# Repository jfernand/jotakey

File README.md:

# Jotakey

A FIDO2 / WebAuthn security key, in the family of the YubiKey, written in Rust and
engineered as security-critical software: tested, fuzzed, mutation-tested, and with its
security-critical state machines proved in Lean 4.

It runs on two platforms:

- **The jotakey key** (`hardware/`): a USB-A dongle with an STM32L432 microcontroller and an
  Infineon OPTIGA Trust M secure element. Hardware 0.3.0 is designed and ready to order; its
  firmware (native USB, touch, and the OPTIGA over its shielded connection) is written and
  tested against a simulated OPTIGA, and awaits a board.
- **The Espressif ESP32-C6 DevKit**: the development platform, where the MVP firmware runs
  today (CTAP 2.0, non-resident credentials, USB through a Linux bridge, and BLE).

## Where to start

| | |
|---|---|
| `docs/jotakey.pdf` | The design report: FIDO and passkeys from first principles, the threat model, the key hierarchy, testing and formal verification. `docs/jotakey-print.pdf` is the same for paper. |
| `AGENTS.md` | The normative rules: security invariants, key hierarchy, coding rules, commands. |
| `hardware/HARDWARE.md` | The board: part choices against their datasheets. |
| `hardware/MANUFACTURING.md` | How to order a hardware release from JLCPCB. |
| `crates/jotakey-core` | The protocol core: `no_std`, no allocation, no `unsafe`. |
| `formal/` | Lean 4 models and proofs. |
| `crates/jotakey-explorer` | `just explore`: a terminal browser for the FIDO keys attached to this computer, any make. |
| `examples/webauthn-topcoat` | A demo web app: register a Jotakey and sign in with it, on `localhost`. |

## Versions

Hardware and firmware are versioned separately: hardware releases are tagged `hw-vX.Y.Z`,
firmware releases `fw-vX.Y.Z`. Each release publishes both versions of the report.

## License

Copyright (c) 2026 Javier Fernandez @ JotaSoft.

Licensed under either of [Apache License, Version 2.0](LICENSE-APACHE) or
[MIT license](LICENSE-MIT), at your option.

Unless you explicitly state otherwise, any contribution intentionally submitted for inclusion
in this work, as defined in the Apache-2.0 license, shall be dual licensed as above, without any
additional terms or conditions.

Third-party documents cited by the design are not part of this repository; see
`docs/references/README.md` and `hardware/datasheets/README.md` for where to obtain them.

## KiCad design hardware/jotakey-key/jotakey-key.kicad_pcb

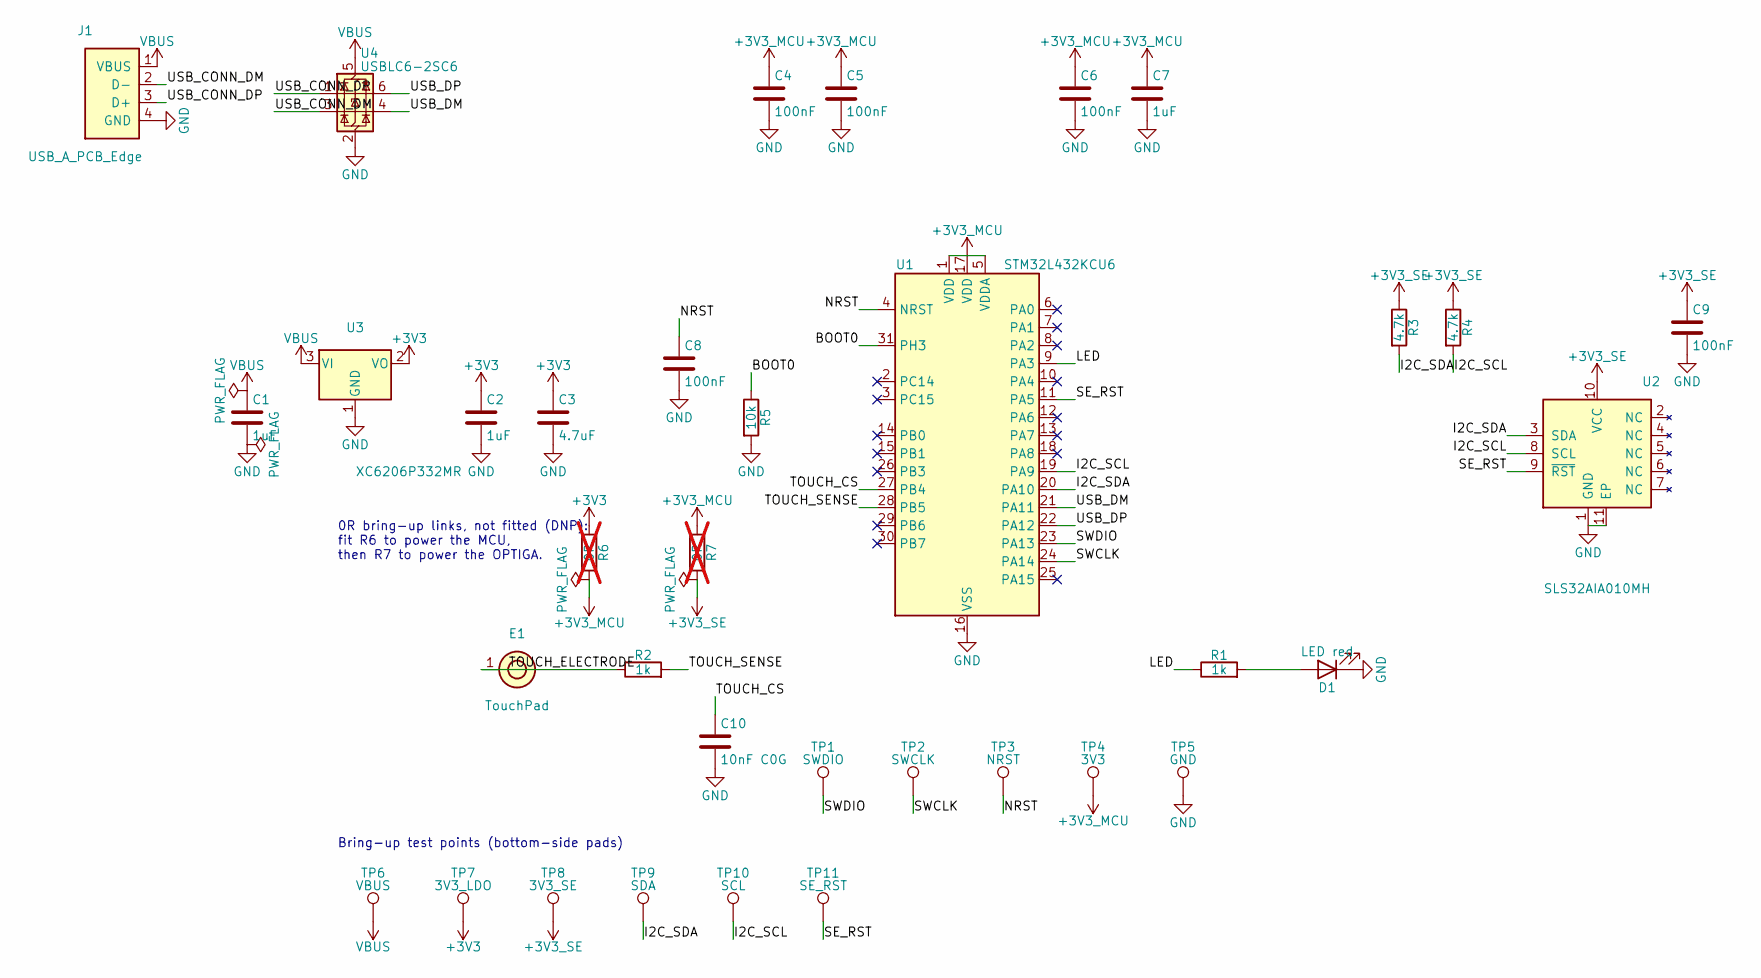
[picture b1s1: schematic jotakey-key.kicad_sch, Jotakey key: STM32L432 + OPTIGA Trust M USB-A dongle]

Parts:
C1, C2, C7: 1uF; C_0402_1005Metric; MPN CL05A105KA5NQNC; LCSC C52923
C3: 4.7uF; C_0603_1608Metric; MPN CL10A475KO8NNNC; LCSC C19666
C4, C5, C6, C8, C9: 100nF; C_0402_1005Metric; MPN CL05B104KO5NNNC; LCSC C1525
C10: 10nF C0G; C_0402_1005Metric; MPN GRM1555C1H103JE01D; LCSC C22400107
D1: LED red; LED_0603_1608Metric; MPN KT-0603R; LCSC C2286
E1: TouchPad; TouchPad_D10mm
J1: USB_A_PCB_Edge; USB_A_PCB_Edge_2.0mm
R1, R2: 1k; R_0402_1005Metric; MPN 0402WGF1001TCE; LCSC C11702
R3, R4: 4.7k; R_0402_1005Metric; MPN 0402WGF4701TCE; LCSC C25900
R5: 10k; R_0402_1005Metric; MPN 0402WGF1002TCE; LCSC C25744
R6, R7: 0R; R_0402_1005Metric; MPN 0402WGF0000TCE; LCSC C17168; not fitted
TP1: SWDIO; TestPoint_Pad_D1.0mm
TP2: SWCLK; TestPoint_Pad_D1.0mm
TP3: NRST; TestPoint_Pad_D1.0mm
TP4: 3V3; TestPoint_Pad_D1.0mm
TP5: GND; TestPoint_Pad_D1.0mm
TP6: VBUS; TestPoint_Pad_D1.0mm
TP7: 3V3_LDO; TestPoint_Pad_D1.0mm
TP8: 3V3_SE; TestPoint_Pad_D1.0mm
TP9: SDA; TestPoint_Pad_D1.0mm
TP10: SCL; TestPoint_Pad_D1.0mm
TP11: SE_RST; TestPoint_Pad_D1.0mm
U1: STM32L432KCU6; QFN-32-1EP_5x5mm_P0.5mm_EP3.45x3.45mm; MPN STM32L432KCU6; LCSC C1337280
U2: SLS32AIA010MH; Infineon_PG-USON-10-2_3x3mm_P0.5mm_EP1.7x2.5mm; MPN SLS32AIA010MH USON10; LCSC C539250
U3: XC6206P332MR; SOT-23-3; MPN XC6206P332MR-G; LCSC C5446
U4: USBLC6-2SC6; SOT-23-6; MPN USBLC6-2SC6; LCSC C7519

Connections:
+3V3: C2.1, C3.1, R6.1, TP7.1 (1_1), U3.2 (VO)
+3V3_MCU: C4.1, C5.1, C6.1, C7.1, R6.2, R7.1, TP4.1 (1_1), U1.1 (VDD), U1.5 (VDDA), U1.17 (VDD)
+3V3_SE: C9.1, R3.1, R4.1, R7.2, TP8.1 (1_1), U2.10 (VCC)
/BOOT0: R5.1, U1.31 (PH3)
/I2C_SCL: R4.2, TP10.1 (1_1), U1.19 (PA9), U2.8 (SCL)
/I2C_SDA: R3.2, TP9.1 (1_1), U1.20 (PA10), U2.3 (SDA)
/LED: R1.1, U1.9 (PA3)
/NRST: C8.1, TP3.1 (1_1), U1.4 (NRST)
/SE_RST: TP11.1 (1_1), U1.11 (PA5), U2.9 (~RST)
/SWCLK: TP2.1 (1_1), U1.24 (PA14)
/SWDIO: TP1.1 (1_1), U1.23 (PA13)
/TOUCH_CS: C10.1, U1.27 (PB4)
/TOUCH_ELECTRODE: E1.1 (~_1), R2.1
/TOUCH_SENSE: R2.2, U1.28 (PB5)
/USB_CONN_DM: J1.2 (D-), U4.3 (I/O2)
/USB_CONN_DP: J1.3 (D+), U4.1 (I/O1)
/USB_DM: U1.21 (PA11), U4.4 (I/O2)
/USB_DP: U1.22 (PA12), U4.6 (I/O1)
GND: C1.2, C2.2, C3.2, C4.2, C5.2, C6.2, C7.2, C8.2, C9.2, C10.2, D1.1 (K), J1.4 (GND), R5.2, TP5.1 (1_1), U1.16 (VSS), U1.32 (VSS), U1.33 (VSS), U2.1 (GND), U2.11 (EP), U3.1 (GND), U4.2 (GND)
unnamed: D1.2 (A), R1.2
VBUS: C1.1, J1.1 (VBUS), TP6.1 (1_1), U3.3 (VI), U4.5 (VBUS)

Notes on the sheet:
0R bring-up links, not fitted (DNP): fit R6 to power the MCU, then R7 to power the OPTIGA.
Bring-up test points (bottom-side pads)

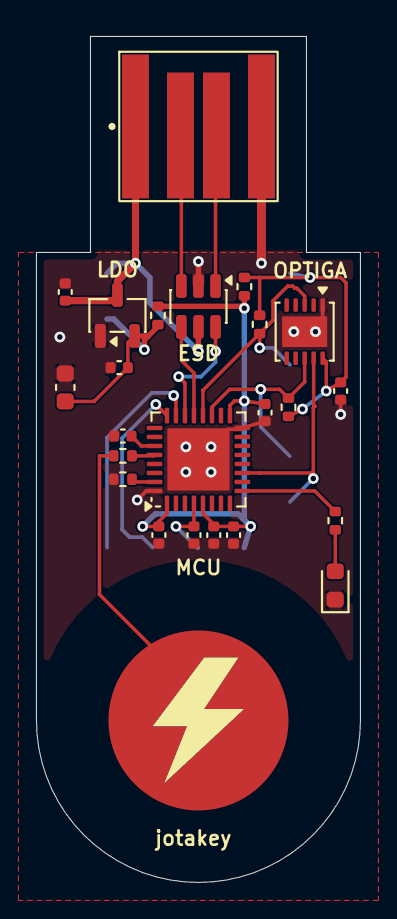
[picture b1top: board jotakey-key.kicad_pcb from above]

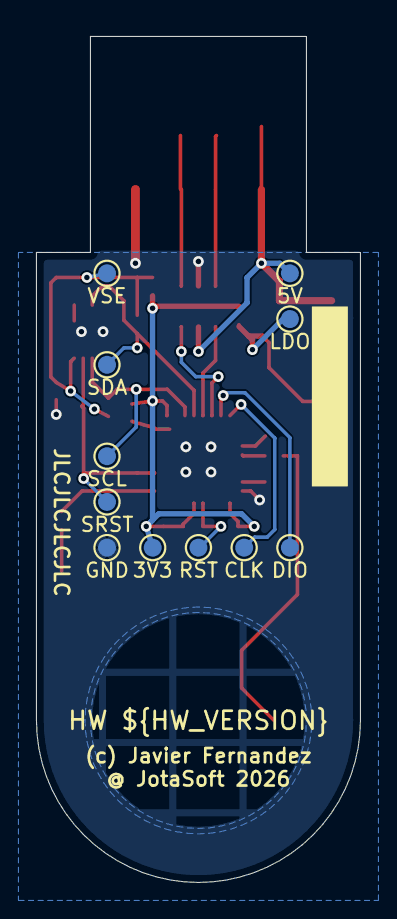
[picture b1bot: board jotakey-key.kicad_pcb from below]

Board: 2 copper layers, 18.0 x 47.0 mm, 35 parts (11 on the bottom side), 21 nets.

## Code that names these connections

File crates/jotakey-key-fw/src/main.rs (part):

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    defmt::info!("jotakey key {} booting", env!("CARGO_PKG_VERSION"));

    // LED first, so faults are visible.
    let led = Output::new(p.PA3, Level::Low, Speed::Low);
    if let Ok(t) = led::led_task(led) {
        spawner.spawn(t);
    }
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    let out = OUT.init([0u8; MAX_MSG_SIZE]);

    // USB starts early so that a faulty key still enumerates and answers CTAP1_ERR_OTHER.
    let driver = stm_usb::Driver::new(p.USB, Irqs, p.PA12, p.PA11);
    interrupt::SPI3.set_priority(Priority::P6);
    let usb_spawner = USB_EXECUTOR.start(interrupt::SPI3);
    if let Ok(t) = usb::usb_task(driver) {
        usb_spawner.spawn(t);
    }

    // Root key: the OPTIGA on I2C1, its reset on PA5.
    #[cfg(not(feature = "dev-key"))]
    let root = {
        let mut i2c_config = embassy_stm32::i2c::Config::default();
        i2c_config.frequency = embassy_stm32::time::Hertz(optiga::I2C_HZ);
        let i2c = embassy_stm32::i2c::I2c::new_blocking(p.I2C1, p.PA9, p.PA10, i2c_config);
        let reset = Output::new(p.PA5, Level::Low, Speed::Low);
        RootKey::Optiga(optiga::SecureElement::new(optiga::OptigaBus::new(i2c), reset))
    };
    // The dev-key build never drives the OPTIGA: its reset line stays low, so that with the
    // bring-up link R7 open nothing back-powers the secure element (HARDWARE.md §1).
    #[cfg(feature = "dev-key")]
    let _optiga_reset = Output::new(p.PA5, Level::Low, Speed::Low);
    #[cfg(feature = "dev-key")]
    let root = {
        defmt::warn!("INSECURE dev-key build: root key derived from the STM32 unique ID");
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    }
    defmt::info!("self tests passed");

    // Touch sensor: TSC group 2, PB4 sampling capacitor, PB5 electrode.
    let mut g2: tsc::pin_groups::PinGroupWithRoles<peripherals::TSC, tsc::pin_groups::G2> =
        tsc::pin_groups::PinGroupWithRoles::default();
    g2.set_io1::<tsc::pin_groups::pin_roles::Sample>(p.PB4);
    let electrode = g2.set_io2::<tsc::pin_groups::pin_roles::Channel>(p.PB5);
    let groups = tsc::pin_groups::PinGroups { g2: Some(g2.pin_group), ..Default::default() };
    let mut sensor = match Tsc::new_blocking(p.TSC, groups, tsc::Config::default()) {
        Ok(t) => TouchSensor::new(t, electrode.pin),
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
